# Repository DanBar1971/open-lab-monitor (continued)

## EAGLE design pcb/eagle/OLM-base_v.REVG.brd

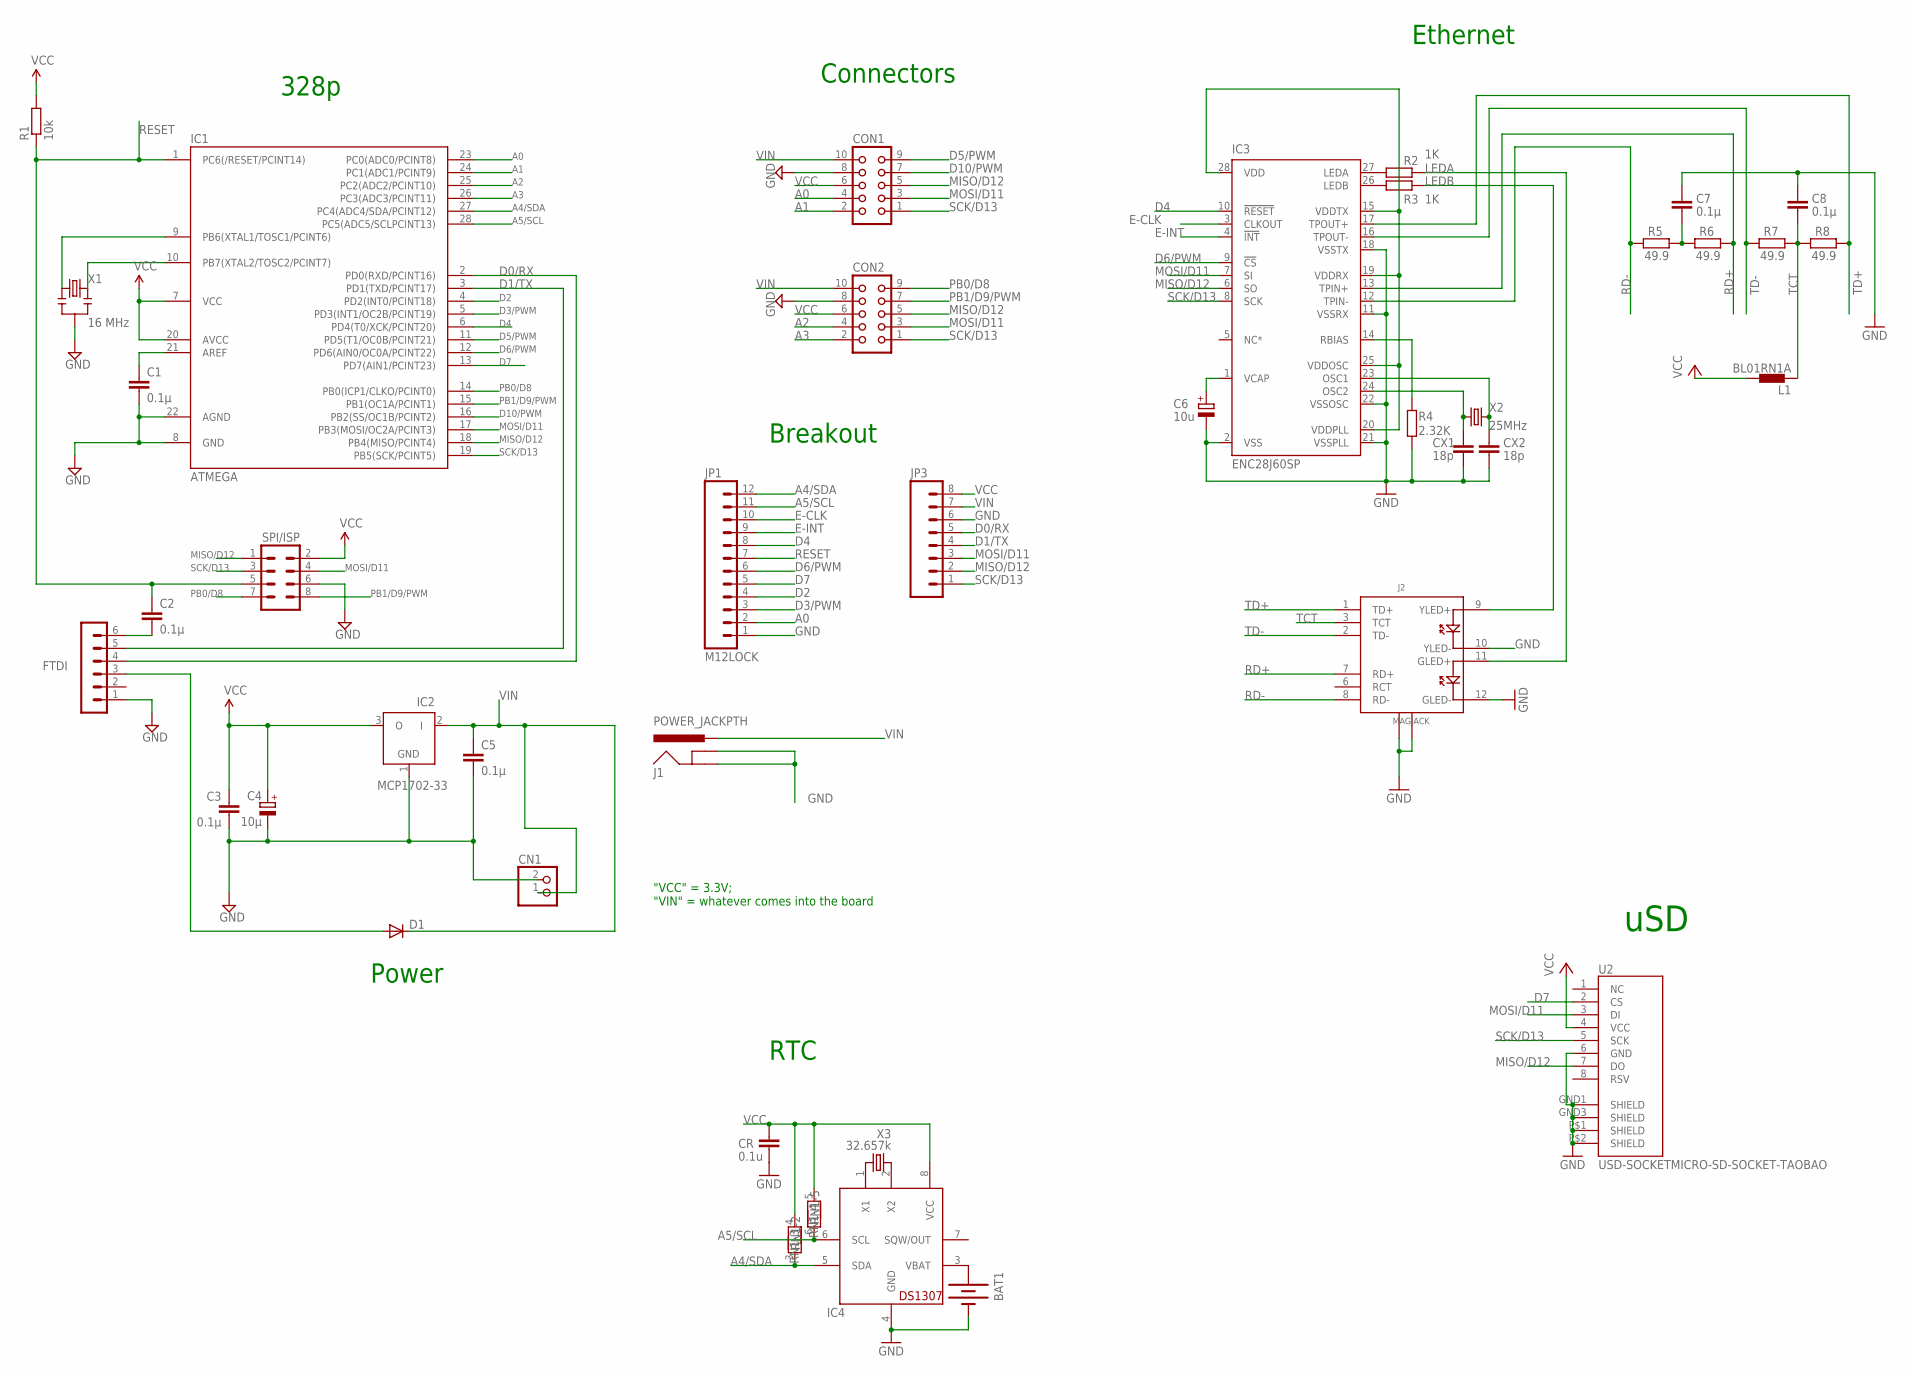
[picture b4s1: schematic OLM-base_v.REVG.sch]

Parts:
BAT1: BATTERY12PTH; BATTCON_12MM_PTH
C1, C2, C3, C5, C7, C8: 0.1µ; C025-024X044
C4: 10µ; E1,8-4
C6: 10u; E1,8-4
CN1: JST_2PIN-THM-RA; JST-PH-2-THM-RA
CON1, CON2: CON10L
CR: 0.1u; C025-024X044
CX1, CX2: 18p; C025-024X044
D1: DIODE-D-5; D-5
FTDI: FTDI; MA06-1
IC1: ATMEGA; DIL28-3
IC2: MCP1702-33; TO92
IC3: ENC28J60SP; DIL28-3
IC4: DS1307; DIL08
J1: POWER_JACKPTH; POWER_JACK_PTH
J2: MAGJACK
JP1: M12LOCK; 1X12_LOCK
JP3: M08LOCK; 1X08_LOCK
L1: BL01RN1A
R1: 10k; 0204/7
R2, R3: 1K; 0204/7
R4: 2.32K; 0204/7
R5, R6, R7, R8: 49.9; 0204/7
RN1: RNX7; RN-8
SV1: SPI/ISP; MA04-2
U2: USD-SOCKETMICRO-SD-SOCKET-TAOBAO; MICRO-SD-SOCKET-TAOBAO
X1: 16 MHz; RESONATOR-PTH
X2: 25MHz; HC49US
X3: 32.657k; TC26H

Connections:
A0: CON1.4, IC1.23 (PC0(ADC0/PCINT8)), JP1.2
A1: CON1.2, IC1.24 (PC1(ADC1/PCINT9))
A2: CON2.4, IC1.25 (PC2(ADC2/PCINT10))
A3: CON2.2, IC1.26 (PC3(ADC3/PCINT11))
A4/SDA: IC1.27 (PC4(ADC4/SDA/PCINT12)), IC4.5 (SDA), JP1.12, RN1.3
A5/SCL: IC1.28 (PC5(ADC5/SCLPCINT13)), IC4.6 (SCL), JP1.11, RN1.6
D0/RX: FTDI.4, IC1.2 (PD0(RXD/PCINT16)), JP3.5
D1/TX: FTDI.5, IC1.3 (PD1(TXD/PCINT17)), JP3.4
D2: IC1.4 (PD2(INT0/PCINT18)), JP1.4
D3/PWM: IC1.5 (PD3(INT1/OC2B/PCINT19)), JP1.3
D4: IC1.6 (PD4(T0/XCK/PCINT20)), IC3.10 (!RESET), JP1.8
D5/PWM: CON1.9, IC1.11 (PD5(T1/OC0B/PCINT21))
D6/PWM: IC1.12 (PD6(AIN0/OC0A/PCINT22)), IC3.9 (!CS), JP1.6
D7: IC1.13 (PD7(AIN1/PCINT23)), JP1.5, U2.2 (CS)
D10/PWM: CON1.7, IC1.16 (PB2(SS/OC1B/PCINT2))
E-CLK: IC3.3 (CLKOUT), JP1.10
E-INT: IC3.4 (!INT), JP1.9
GND: BAT1.GND (-), C1.2, C3.2, C4.-, C5.2, C6.-, C7.1, C8.1, CN1.2 (1), CON1.8, CON2.8, CR.2, CX1.2, CX2.2, FTDI.1, IC1.8 (GND), IC1.22 (AGND), IC2.1 (GND), IC3.2 (VSS), IC3.11 (VSSRX), IC3.18 (VSSTX), IC3.21 (VSSPLL), IC3.22 (VSSOSC), IC4.4 (GND), J1.GND, J1.GNDBREAK, J2.10 (YLED-), J2.12 (GLED-), J2.M1 (GND1), J2.M2 (GND2), JP1.1, JP3.6, R4.2, SV1.6, U2.6 (GND), U2.GND1 (SHIELD), U2.GND3 (SHIELD), U2.P$1 (SHIELD), U2.P$2 (SHIELD), X1.2
LEDA: J2.11 (GLED+), R2.2
LEDB: J2.9 (YLED+), R3.2
MISO/D12: CON1.5, CON2.5, IC1.18 (PB4(MISO/PCINT4)), IC3.6 (SO), JP3.2, SV1.1, U2.7 (DO)
MOSI/D11: CON1.3, CON2.3, IC1.17 (PB3(MOSI/OC2A/PCINT3)), IC3.7 (SI), JP3.3, SV1.4, U2.3 (DI)
unnamed: IC1.9 (PB6(XTAL1/TOSC1/PCINT6)), X1.1
unnamed: D1.A, FTDI.3
unnamed: C1.1, IC1.21 (AREF)
unnamed: C2.2, FTDI.6
unnamed: IC1.10 (PB7(XTAL2/TOSC2/PCINT7)), X1.3
unnamed: BAT1.VCC@1 (+), IC4.3 (VBAT)
unnamed: IC3.27 (LEDA), R2.1
unnamed: IC3.26 (LEDB), R3.1
unnamed: IC4.2 (X2), X3.2
unnamed: C6.+, IC3.1 (VCAP)
unnamed: IC3.14 (RBIAS), R4.1
unnamed: CX1.1, IC3.24 (OSC2), X2.1
unnamed: CX2.1, IC3.23 (OSC1), X2.2
unnamed: C7.2, R5.2, R6.1
unnamed: IC4.1 (X1), X3.1
PB0/D8: CON2.9, IC1.14 (PB0(ICP1/CLKO/PCINT0)), SV1.7
PB1/D9/PWM: CON2.7, IC1.15 (PB1(OC1A/PCINT1)), SV1.8
RD+: IC3.13 (TPIN+), J2.7 (RD+), R6.2
RD-: IC3.12 (TPIN-), J2.8 (RD-), R5.1
RESET: C2.1, IC1.1 (PC6(/RESET/PCINT14)), JP1.7, R1.1, SV1.5
SCK/D13: CON1.1, CON2.1, IC1.19 (PB5(SCK/PCINT5)), IC3.8 (SCK), JP3.1, SV1.3, U2.5 (SCK)
TCT: C8.2, J2.3 (TCT), L1.1, R7.2, R8.1
TD+: IC3.17 (TPOUT+), J2.1 (TD+), R8.2
TD-: IC3.16 (TPOUT-), J2.2 (TD-), R7.1
VCC: C3.1, C4.+, CON1.6, CON2.6, CR.1, IC1.7 (VCC), IC1.20 (AVCC), IC2.3 (O), IC3.15 (VDDTX), IC3.19 (VDDRX), IC3.20 (VDDPLL), IC3.25 (VDDOSC), IC3.28 (VDD), IC4.8 (VCC), JP3.8, L1.2, R1.2, RN1.4, RN1.5, SV1.2, U2.4 (VCC)
VIN: C5.1, CN1.1 (2), CON1.10, CON2.10, D1.C, IC2.2 (I), J1.PWR, JP3.7

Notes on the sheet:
328p
Connectors
Power
"VCC" = 3.3V; "VIN" = whatever comes into the board
Breakout
Ethernet
RTC
uSD

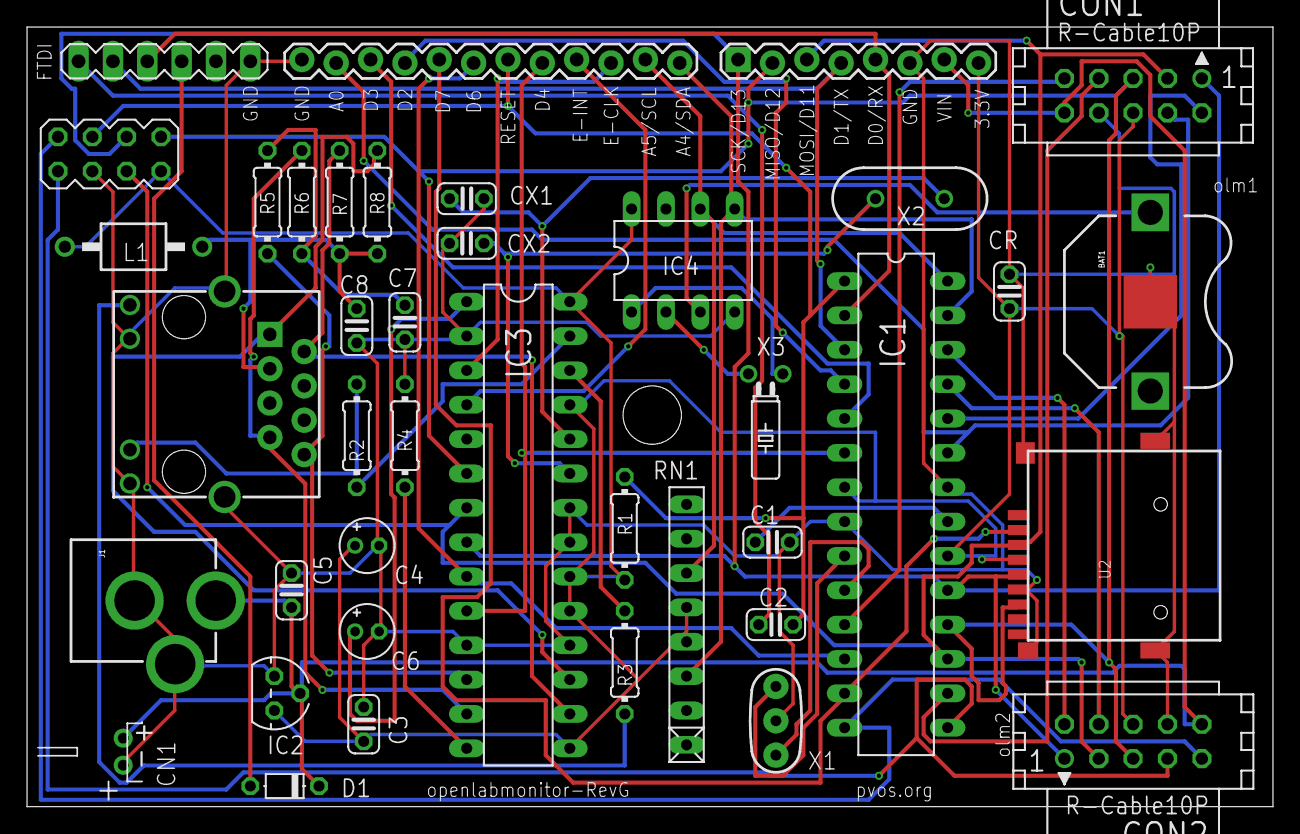
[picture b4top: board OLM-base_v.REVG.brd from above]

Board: 2 copper layers, 92.1 x 57.6 mm, 40 parts (0 on the bottom side), 48 nets.

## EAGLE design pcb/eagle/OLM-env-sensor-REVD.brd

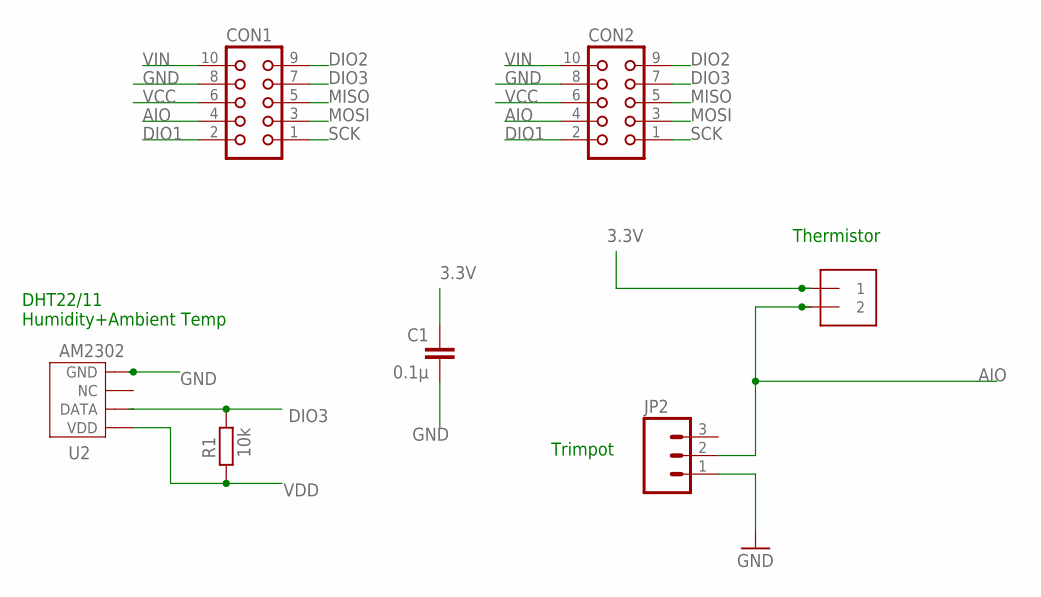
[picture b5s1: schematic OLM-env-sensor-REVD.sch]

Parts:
C1: 0.1µ; C025-024X044
CON1, CON2: CON10L
J1: 1X2-3.5MM
JP2: M03PTH; 1X03
R1: 10k; 0204/7
U2: AM2302

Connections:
3.3V: C1.1, J1.1
AIO: CON1.4, CON2.4, J1.2, JP2.2
DIO1: CON1.2, CON2.2
DIO2: CON1.9, CON2.9
DIO3: CON1.7, CON2.7, R1.2, U2.P$2 (DATA)
GND: C1.2, CON1.8, CON2.8, JP2.1, U2.P$4 (GND)
MISO: CON1.5, CON2.5
MOSI: CON1.3, CON2.3
SCK: CON1.1, CON2.1
VCC: CON1.6, CON2.6
VDD: R1.1, U2.P$1 (VDD)
VIN: CON1.10, CON2.10

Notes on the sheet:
Thermistor
DHT22/11 Humidity+Ambient Temp
Trimpot

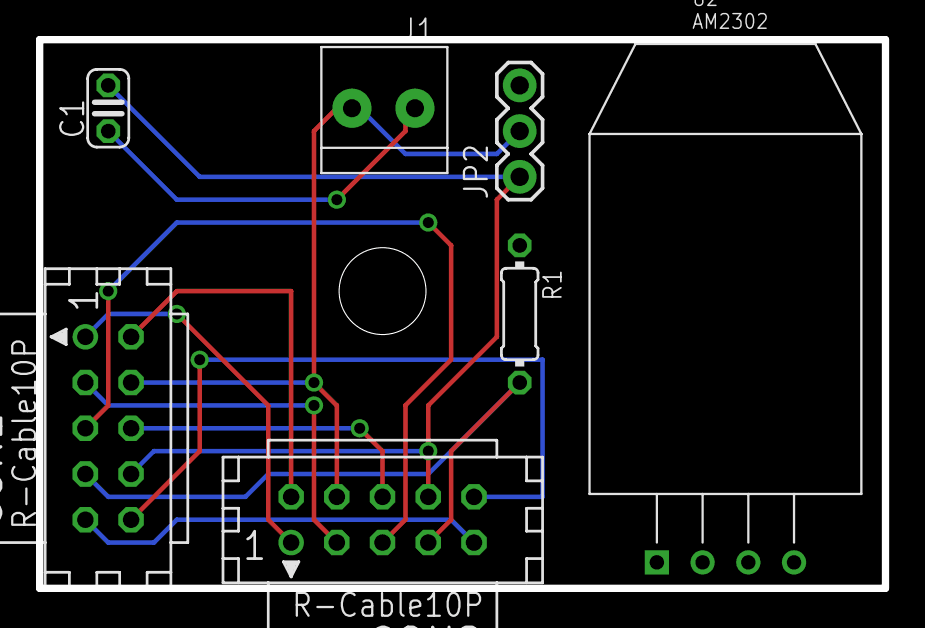
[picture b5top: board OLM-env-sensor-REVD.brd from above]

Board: 2 copper layers, 47.0 x 30.5 mm, 7 parts (0 on the bottom side), 12 nets.

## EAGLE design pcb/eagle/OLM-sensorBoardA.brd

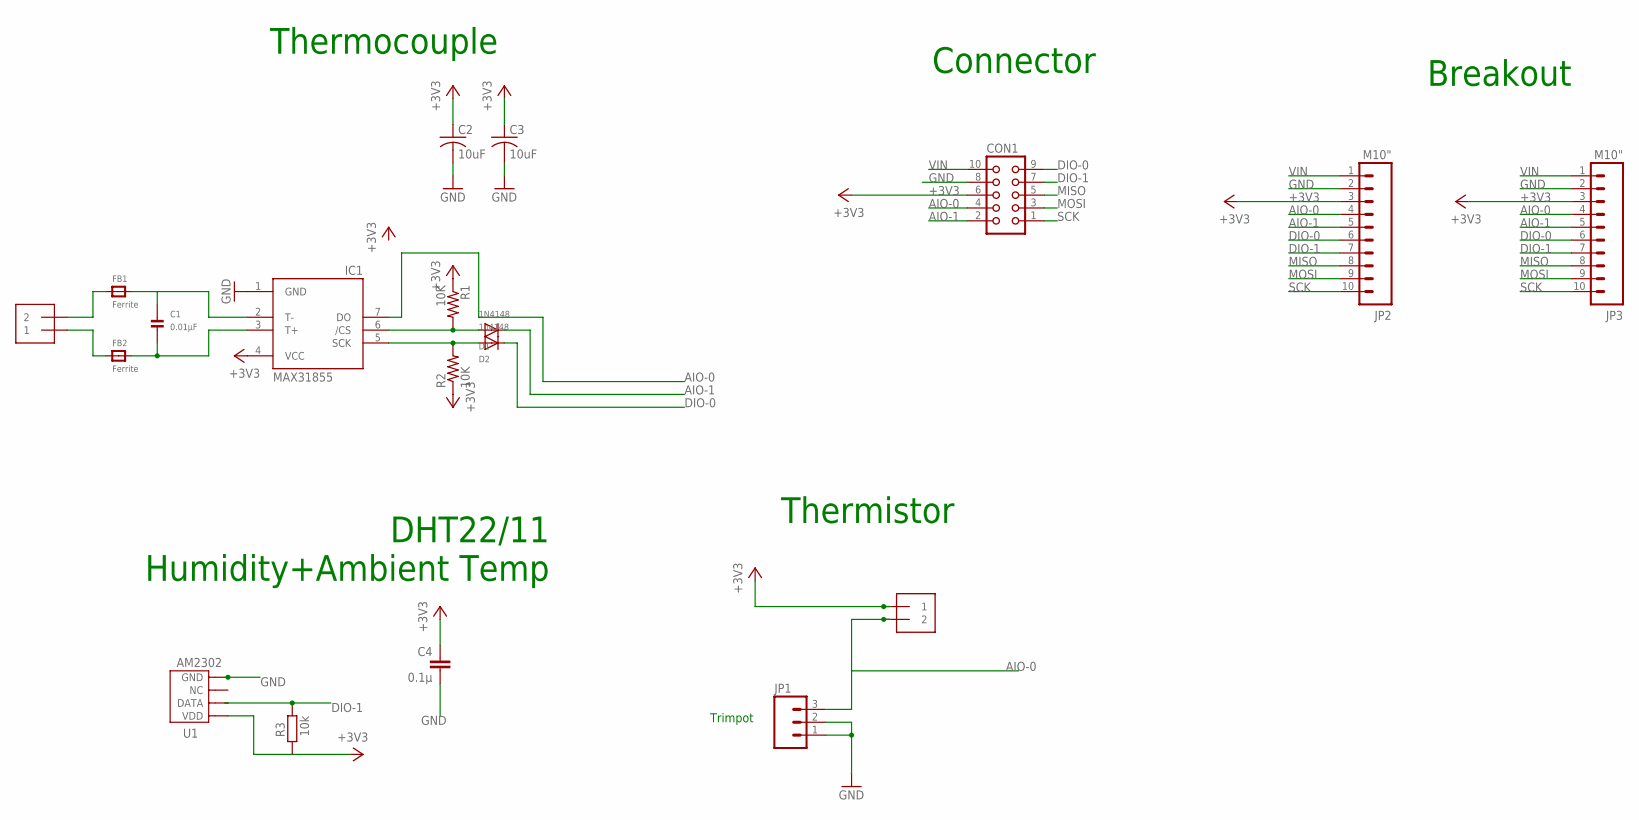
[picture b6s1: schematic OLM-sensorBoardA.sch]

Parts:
C1: 0.01µF; _0805
C2, C3: 10uF; C0805K
C4: 0.1µ; C025-024X044
CON1: CON10L
D1: 1N4148; SOD-323F
D2: 1n4148; SOD-323F
FB1, FB2: Ferrite; _0805
IC1: MAX31855; SO08
J1, J2: 1X2-3.5MM
JP1: M03PTH; 1X03
JP2, JP3: M10"; 1X10
R1, R2: 10K; R0805
R3: 10k; 0204/7
U1: AM2302

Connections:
+3V3: C2.1, C3.1, C4.1, CON1.6, IC1.4 (VCC), J2.1, JP2.3, JP3.3, R1.1, R2.1, R3.1, U1.P$1 (VDD)
AIO-0: CON1.4, IC1.7 (DO), J2.2, JP1.3, JP2.4, JP3.4
AIO-1: CON1.2, D1.C, JP2.5, JP3.5
CS: D1.A, IC1.6 (/CS), R1.2
DIO-0: CON1.9, D2.C, JP2.6, JP3.6
DIO-1: CON1.7, JP2.7, JP3.7, R3.2, U1.P$2 (DATA)
GND: C2.2, C3.2, C4.2, CON1.8, IC1.1 (GND), JP1.1, JP1.2, JP2.2, JP3.2, U1.P$4 (GND)
MISO: CON1.5, JP2.8, JP3.8
MOSI: CON1.3, JP2.9, JP3.9
unnamed: FB1.1, J1.2
unnamed: C1.1, FB1.2, IC1.2 (T-)
unnamed: FB2.1, J1.1
unnamed: C1.2, FB2.2, IC1.3 (T+)
SCK: CON1.1, D2.A, IC1.5 (SCK), JP2.10, JP3.10, R2.2
VIN: CON1.10, JP2.1, JP3.1

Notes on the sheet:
Thermistor
DHT22/11 Humidity+Ambient Temp
Trimpot
Thermocouple
Connector
Breakout

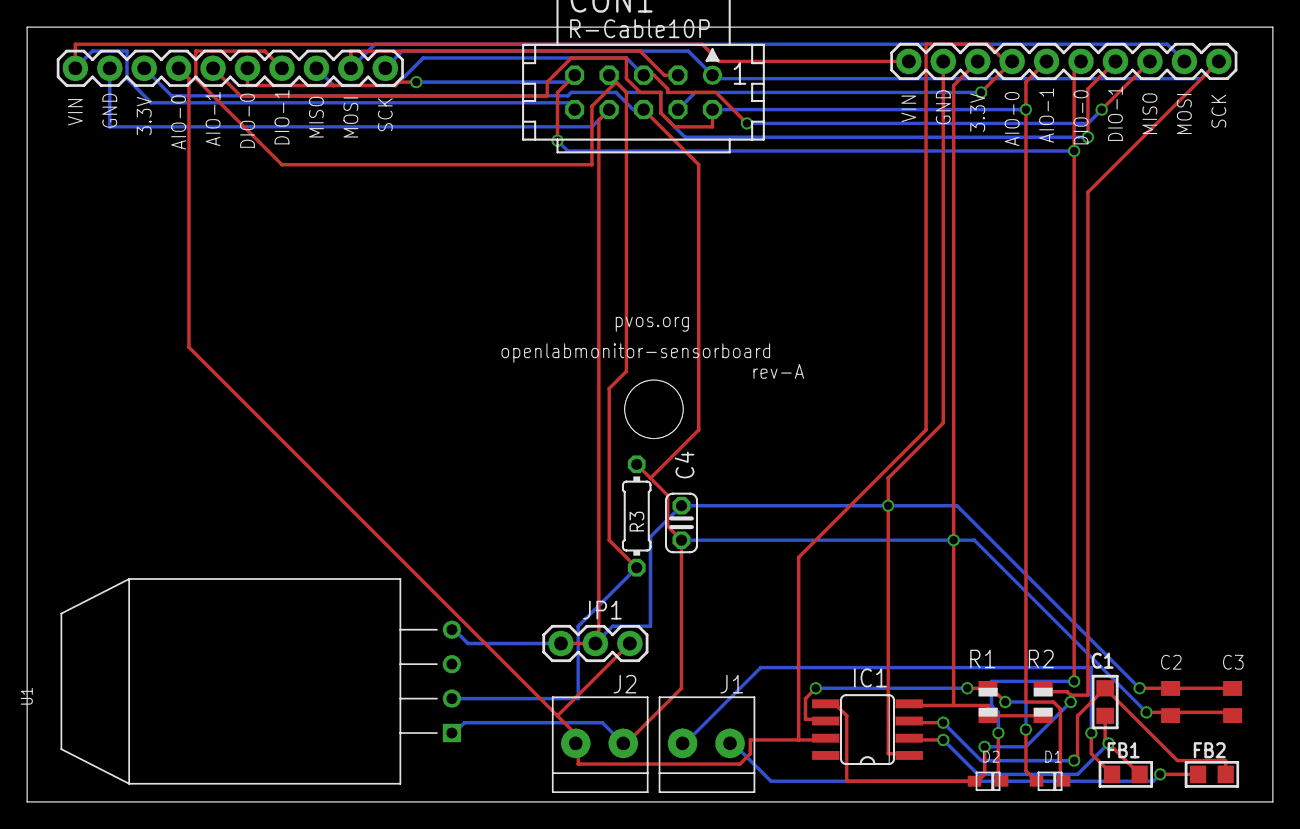
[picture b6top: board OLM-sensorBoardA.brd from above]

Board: 2 copper layers, 91.9 x 57.1 mm, 19 parts (0 on the bottom side), 15 nets.

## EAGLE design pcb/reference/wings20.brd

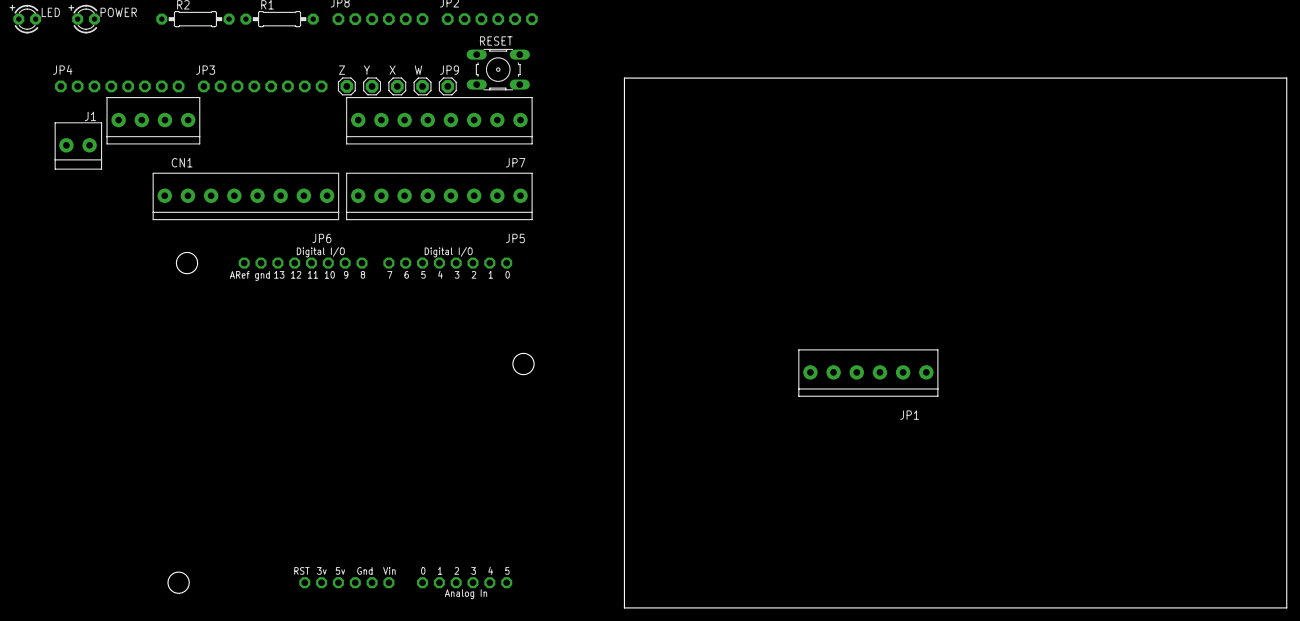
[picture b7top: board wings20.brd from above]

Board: 2 copper layers, 100.0 x 80.0 mm, 21 parts (0 on the bottom side), 33 nets, no tracks yet.

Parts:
CN1: 1X4-3.5MM; 1X04-3.5MM
J1: 1X2-3.5MM
JP1: 1X06-3.5MM
JP2, JP8: 1X06-CLEANBIG
JP3, JP4: 1X08-CLEANBIG
JP5, JP6, JP7: 1X08-3.5MM
JP9: 1X01
LED: LED3MM
POWER: LED3MM
R1, R2: 0207/10
RESET: B3F-10XX
U$1: ARDUINO-BPLACE
W: 1X01
X: 1X01
Y: 1X01
Z: 1X01

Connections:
3V: JP1.2, JP8.5, U$1.3V
GND: J1.1, J1.2, JP1.4, JP1.5, JP4.2, JP6.7, JP7.7, JP7.8, JP8.2, JP8.3, R1.1, R2.1, RESET.3, RESET.4, U$1.GND, U$1.GND1, U$1.GND2
unnamed: JP3.1, JP5.8, U$1.D7
unnamed: JP3.2, JP5.7, U$1.D6
unnamed: JP3.3, JP5.6, U$1.D5
unnamed: JP3.4, JP5.5, U$1.D4
unnamed: JP3.5, JP5.4, U$1.D3
unnamed: JP3.6, JP5.3, U$1.D2
unnamed: JP3.7, JP5.2, U$1.D1
unnamed: JP3.8, JP5.1, U$1.D0
unnamed: JP4.1, JP6.8, U$1.AREF
unnamed: LED.K, R1.2
unnamed: JP4.3, JP6.6, U$1.D13
unnamed: JP4.4, JP6.5, U$1.D12
unnamed: JP4.5, JP6.4, U$1.D11
unnamed: JP4.6, JP6.3, U$1.D10
unnamed: JP4.7, JP6.2, U$1.D9
unnamed: JP4.8, JP6.1, U$1.D8
unnamed: JP2.1, JP7.6, U$1.A5
unnamed: JP2.2, JP7.5, U$1.A4
unnamed: JP2.3, JP7.4, U$1.A3
unnamed: JP2.4, JP7.3, U$1.A2
unnamed: JP2.5, JP7.2, U$1.A1
unnamed: JP2.6, JP7.1, U$1.A0
unnamed: POWER.K, R2.2
unnamed: JP9.1, LED.A
unnamed: CN1.4, Z.1
unnamed: JP1.1, JP8.6, RESET.1, RESET.2, U$1.RESET
unnamed: CN1.3, Y.1
unnamed: CN1.2, X.1
unnamed: CN1.1, W.1
VCC: JP1.3, JP8.4, POWER.A, U$1.5V
VIN: JP1.6, JP8.1, U$1.VIN
